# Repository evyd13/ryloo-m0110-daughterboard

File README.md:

# Ryloo m0110 daughterboard
Daughterboard for the Ryloo "Hello" M0110 keyboard, compatible with the Unified Daughterboard standard.

## BOM

| LCSC part # | Description   | Value | Package  | Amount |
| ----------- | ------------- | ----- | -------- | ------:|
| C27834      | Resistor      | 5.1k  | 0805     | 2      |
| C261942     | Fuse          |       | 0805     | 1      |
| C7519       | ESD prot.     |       | SOT32-6  | 1      |
| C165948     | USB-C conn.   |       |          | 1      |
| C160404     | JST SH 1x4    |       |          | 1      |

Use at your own risk.

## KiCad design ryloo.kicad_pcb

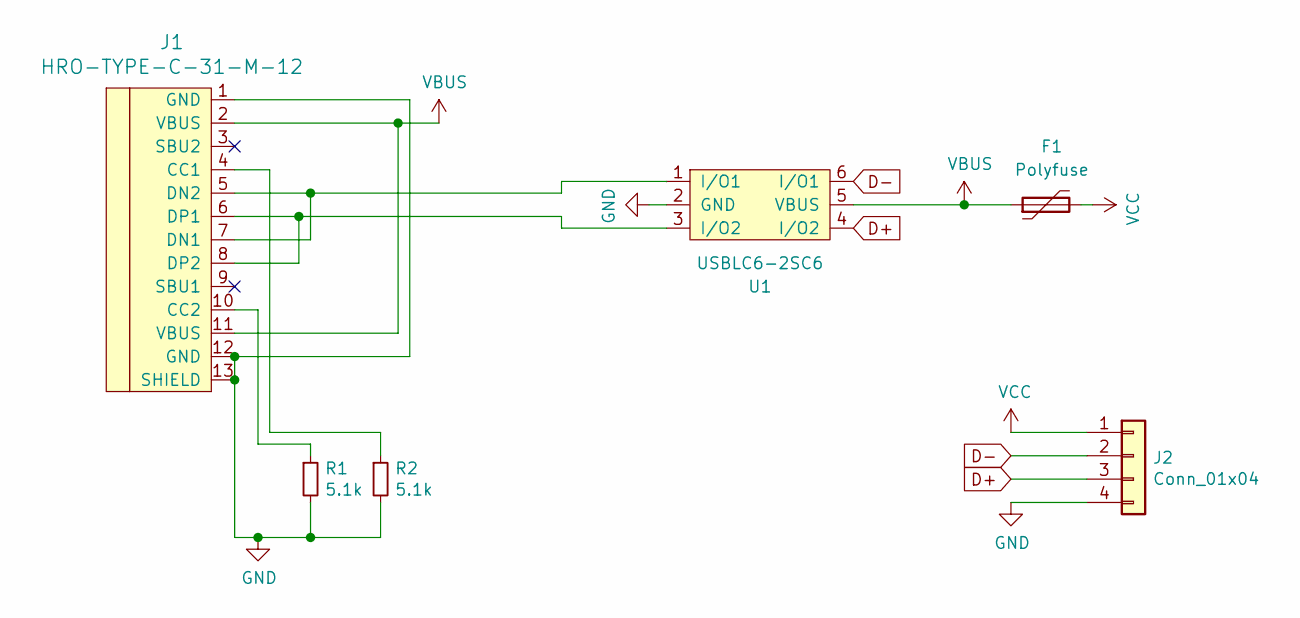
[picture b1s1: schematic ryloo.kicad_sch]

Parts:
F1: Polyfuse; F_0805
J1: HRO-TYPE-C-31-M-12; CONN_HRO-TYPE-C-31-M-12
J2: Conn_01x04; CONN_JST_SH_SM04B-SRSS-TB_1x04-1MP_P1.00mm_Horizontal
R1, R2: 5.1k; R_0805
U1: USBLC6-2SC6; PACKAGE_SOT-23-6

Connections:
D+: J2.3, U1.4 (I/O2)
D-: J2.2, U1.6 (I/O1)
GND: J1.1 (GND), J1.12 (GND), J1.13 (SHIELD), J2.4, R1.2, R2.2, U1.2 (GND)
unnamed: J1.4 (CC1), R2.1
unnamed: J1.5 (DN2), J1.7 (DN1), U1.1 (I/O1)
unnamed: J1.6 (DP1), J1.8 (DP2), U1.3 (I/O2)
unnamed: J1.10 (CC2), R1.1
VBUS: F1.1, J1.2 (VBUS), J1.11 (VBUS), U1.5 (VBUS)
VCC: F1.2, J2.1

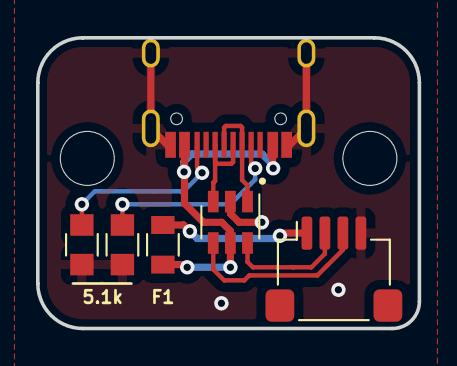
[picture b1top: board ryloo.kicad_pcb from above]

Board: 2 copper layers, 21.2 x 16.1 mm, 6 parts (0 on the bottom side), 9 nets.

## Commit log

2022-02-01 Upload rev1 files
2022-02-01 Upload rev2 files
2022-02-01 Add license
2022-07-07 QOL improvements
